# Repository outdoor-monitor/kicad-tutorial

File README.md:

# kicad-tutorial
Work from Tech Explorations Tutorial on Kicad

Here is a change.

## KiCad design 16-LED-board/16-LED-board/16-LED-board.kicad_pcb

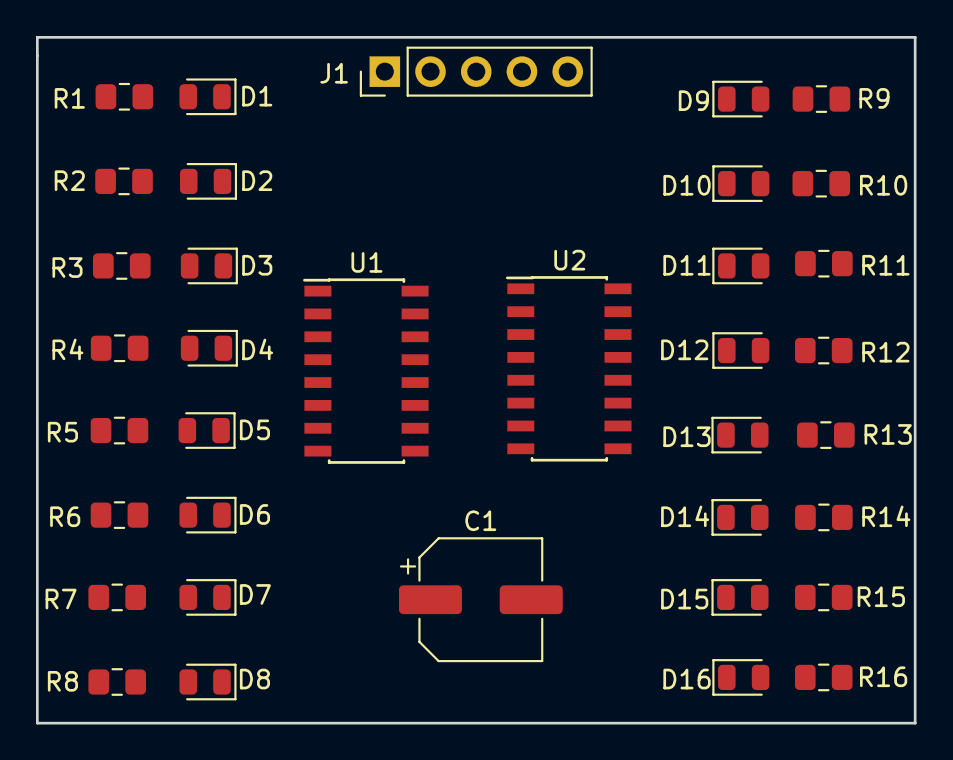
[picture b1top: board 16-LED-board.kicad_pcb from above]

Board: 2 copper layers, 48.8 x 38.1 mm, 36 parts (0 on the bottom side), 38 nets, no tracks yet.

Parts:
C1: 200uF; CP_Elec_6.3x5.3
D1, D2, D3, D4, D5, D6, D7, D8, D9, D10, D11, D12, D13, D14, D15, D16: LED; LED_0805_2012Metric
J1: Conn_01x05_Male; PinHeader_1x05_P2.54mm_Vertical
R1, R2, R3, R4, R5, R6, R7, R8, R9, R10, R11, R12, R13, R14, R15, R16: 220; R_0805_2012Metric_Pad1.15x1.40mm_HandSolder
U1, U2: 74HC595; SOIC-16_3.9x9.9mm_P1.27mm

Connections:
/CLOCK: J1.4, U1.11, U2.11
/DATA: J1.5, U1.14
/DATA_S: U1.9, U2.14
/LATCH: J1.3, U1.12, U2.12
/LED_1_1: D1.1, U1.15
/LED_1_2: D2.1, U1.1
/LED_1_3: D3.1, U1.2
/LED_1_4: D4.1, U1.3
/LED_1_5: D5.1, U1.4
/LED_1_6: D6.1, U1.5
/LED_1_7: D7.1, U1.6
/LED_1_8: D8.1, U1.7
/LED_2_1: D9.1, U2.15
/LED_2_2: D10.1, U2.1
/LED_2_3: D11.1, U2.2
/LED_2_4: D12.1, U2.3
/LED_2_5: D13.1, U2.4
/LED_2_6: D14.1, U2.5
/LED_2_7: D15.1, U2.6
/LED_2_8: D16.1, U2.7
GND: C1.2, J1.2, U1.8, U2.8
unnamed: D1.2, R1.2
unnamed: D2.2, R2.2
unnamed: D3.2, R3.2
unnamed: D4.2, R4.2
unnamed: D5.2, R5.2
unnamed: D6.2, R6.2
unnamed: D7.2, R7.2
unnamed: D8.2, R8.2
unnamed: D9.2, R9.2
unnamed: D10.2, R10.2
unnamed: D11.2, R11.2
unnamed: D12.2, R12.2
unnamed: D13.2, R13.2
unnamed: D14.2, R14.2
unnamed: D15.2, R15.2
unnamed: D16.2, R16.2
VCC: C1.1, J1.1, R1.1, R2.1, R3.1, R4.1, R5.1, R6.1, R7.1, R8.1, R9.1, R10.1, R11.1, R12.1, R13.1, R14.1, R15.1, R16.1, U1.10, U1.16, U2.10, U2.16

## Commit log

2019-01-30 Added a small change
2019-01-31 schematic complete, placement done
